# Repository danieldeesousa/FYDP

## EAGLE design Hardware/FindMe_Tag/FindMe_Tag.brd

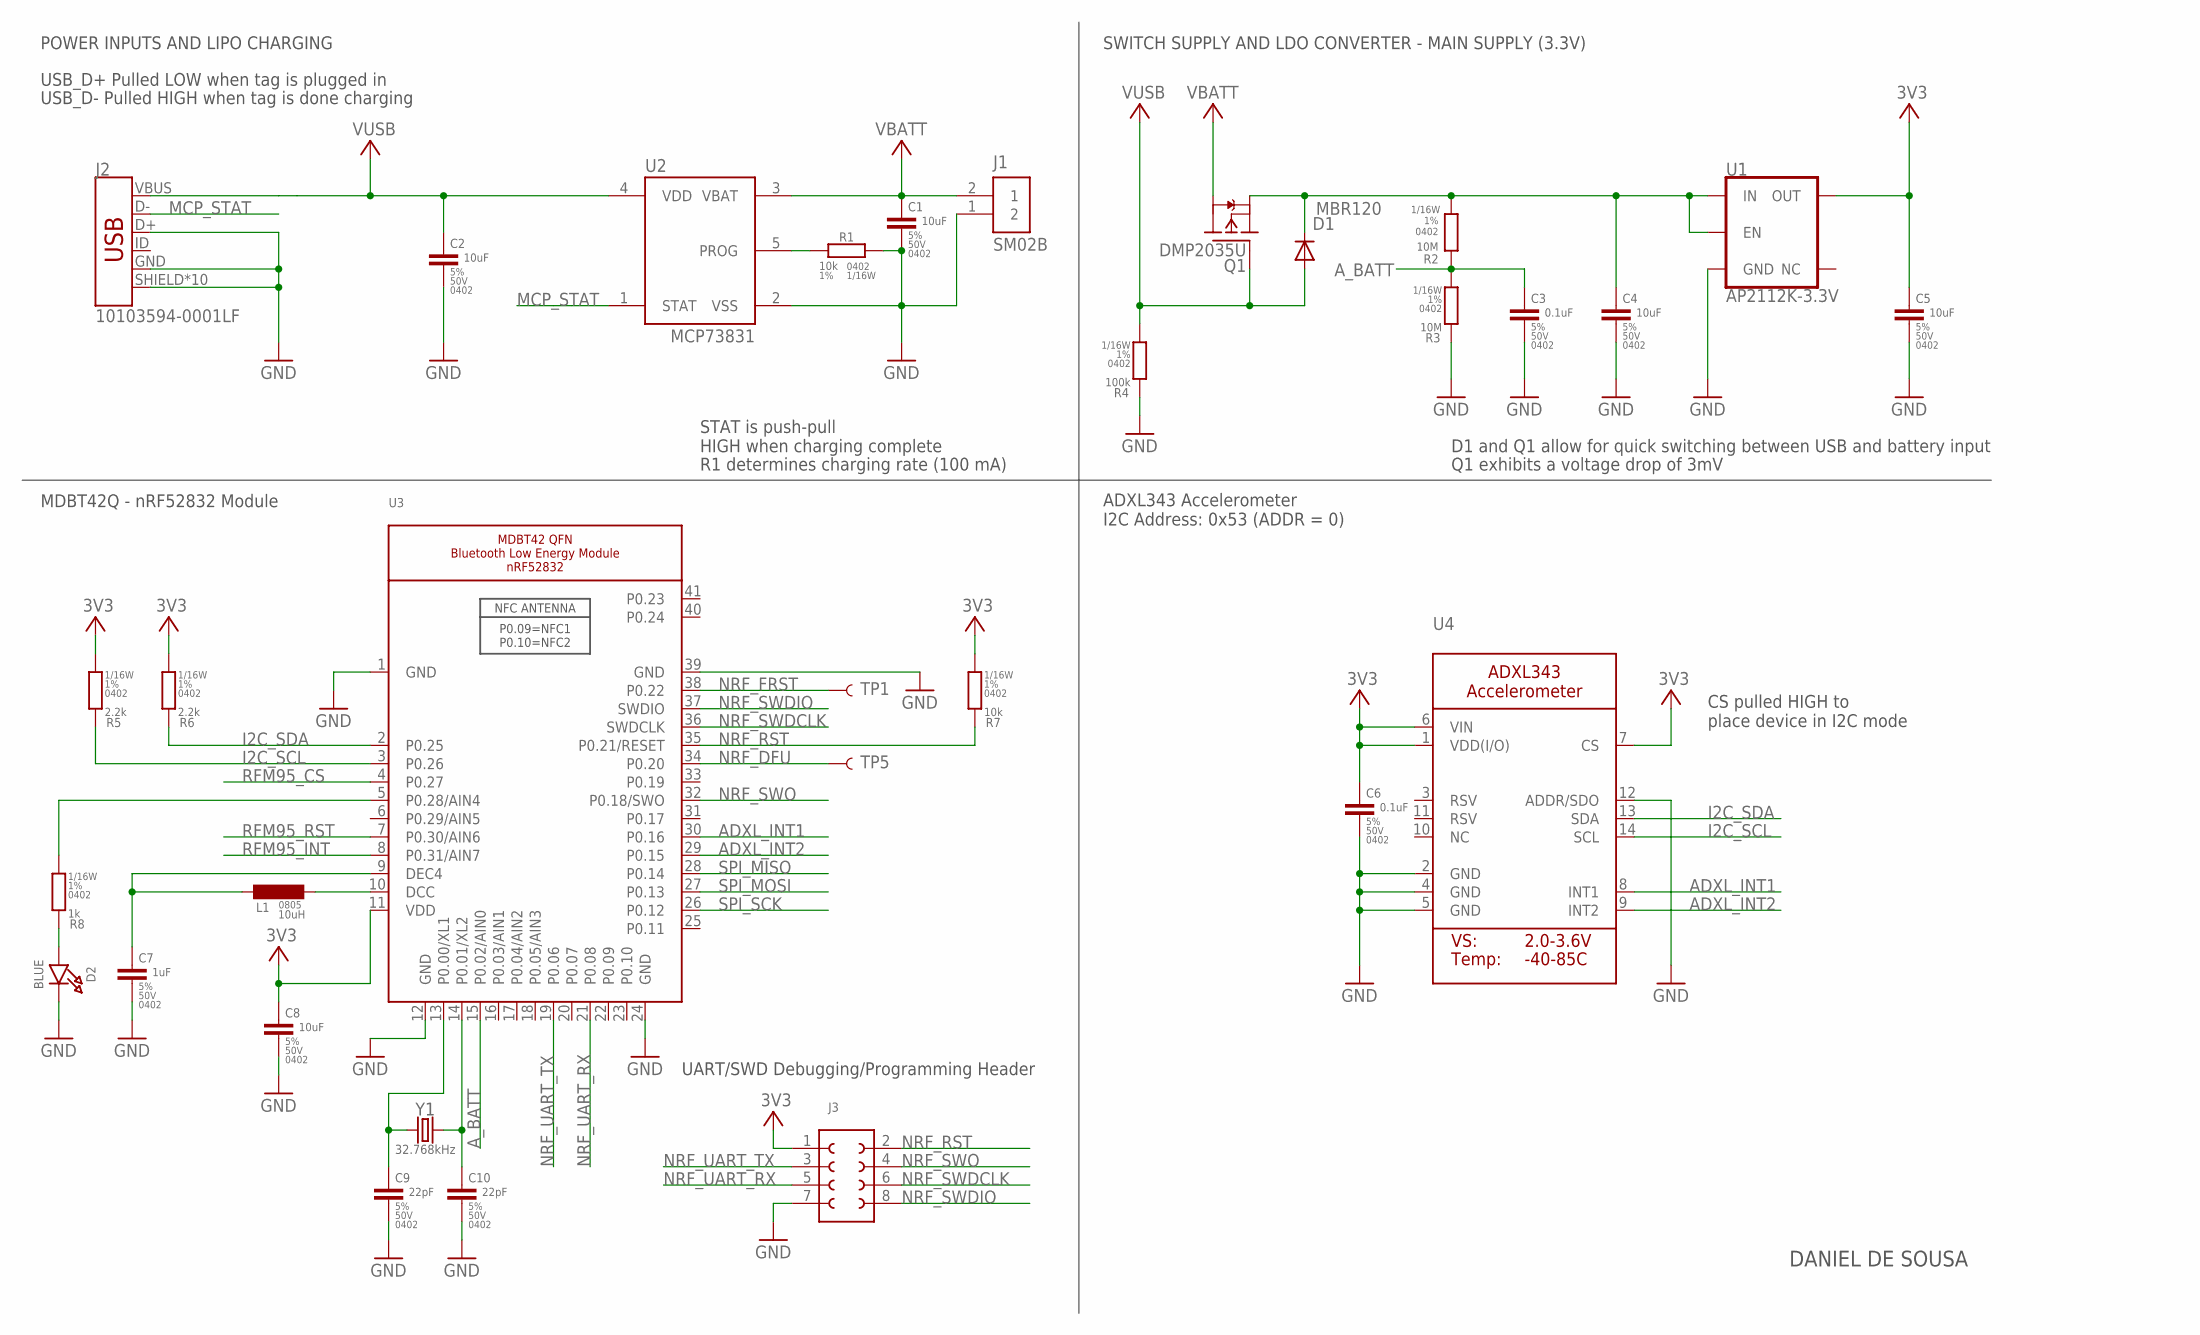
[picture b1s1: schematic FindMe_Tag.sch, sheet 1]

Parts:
C1, C2, C4, C5, C8: 10uF; C0402_MURATA_GRM15-GJM15
C3, C6: 0.1uF; C0402_MURATA_GRM15-GJM15
C7: 1uF; C0402_MURATA_GRM15-GJM15
C9, C10: 22pF; C0402_MURATA_GRM15-GJM15
D1: MBR120; SOD-123FL
D2: BLUE; CHIPLED_0805_NOOUTLINE
J1: SM02B; JST_SH_2X1
J2: 10103594-0001LF; USB-MICROB-PTH-MILL
J3: 610X08243021
L1: 10uH; L0805_MURATA_LQM21
Q1: DMP2035U; SOT23
R1, R7: 10k; R0402_VISHAY_CRCW0402
R2, R3: 10M; R0402_VISHAY_CRCW0402
R4: 100k; R0402_VISHAY_CRCW0402
R5, R6: 2.2k; R0402_VISHAY_CRCW0402
R8: 1k; R0402_VISHAY_CRCW0402
TP1, TP5: TEST-POINT3; PAD.03X.03
U1: AP2112K-3.3V; SOT23-5
U2: MCP73831; SOT-23
U3: NRF52832_MODULE_MDBT42; BLE_MODULE_RAYTAC_MDBT42
U4: ACCEL_ADXL343; LGA14
Y1: 32.768kHz; CRYSTAL-SMD-3.2X1.5MM

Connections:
+3V3: C5.1, C6.1, C8.1, J3.1, R5.2, R6.2, R7.2, U1.5 (OUT), U3.11 (VDD), U4.1 (VDD(I/O)), U4.6 (VIN), U4.7 (CS); also elsewhere on the board
ADXL_INT1: U3.30 (P0.16), U4.8 (INT1)
ADXL_INT2: U3.29 (P0.15), U4.9 (INT2)
A_BATT: C3.1, R2.1, R3.2, U3.15 (P0.02/AIN0)
GND: C1.2, C2.2, C3.2, C4.2, C5.2, C6.2, C7.2, C8.2, C9.2, C10.2, D2.C, J1.1 (2), J2.D+, J2.GND, J2.SHIELD, J2.SHIELD2 (SHIELD), J2.SHIELD3 (SHIELD), J2.SHIELD4 (SHIELD), J2.SHIELD5 (SHIELD), J2.SHIELD6 (SHIELD), J2.SHIELD7 (SHIELD), J2.SHIELD8 (SHIELD), J2.SHIELD9 (SHIELD), J2.SHIELD10 (SHIELD), J3.7 (4), R1.1, R3.1, R4.1, U1.2 (GND), U2.2 (VSS), U3.1 (GND), U3.12 (GND), U3.24 (GND), U3.39 (GND), U4.2 (GND), U4.4 (GND), U4.5 (GND), U4.12 (ADDR/SDO); also elsewhere on the board
I2C_SCL: R5.1, U3.3 (P0.26), U4.14 (SCL); also elsewhere on the board
I2C_SDA: R6.1, U3.2 (P0.25), U4.13 (SDA); also elsewhere on the board
MCP_STAT: J2.D-, U2.1 (STAT)
unnamed: R1.2, U2.5 (PROG)
unnamed: C4.1, D1.C, Q1.E (S), R2.2, U1.1 (IN), U1.3 (EN)
unnamed: C9.1, U3.13 (P0.00/XL1), Y1.P$1 (1)
unnamed: C10.1, U3.14 (P0.01/XL2), Y1.P$2 (2)
unnamed: L1.P$2 (2), U3.10 (DCC)
unnamed: C7.1, L1.P$1 (1), U3.9 (DEC4)
unnamed: R8.2, U3.5 (P0.28/AIN4)
unnamed: D2.A, R8.1
NRF_DFU: TP5.P$1, U3.34 (P0.20)
NRF_FRST: TP1.P$1, U3.38 (P0.22)
NRF_RST: J3.2 (8), R7.1, U3.35 (P0.21/RESET)
NRF_SWDCLK: J3.6, U3.36 (SWDCLK)
NRF_SWDIO: J3.8 (5), U3.37 (SWDIO)
NRF_SWO: J3.4 (7), U3.32 (P0.18/SWO)
NRF_UART_RX: J3.5 (3), U3.21 (P0.08)
NRF_UART_TX: J3.3 (2), U3.19 (P0.06)
RFM95_CS: U3.4 (P0.27); also elsewhere on the board
RFM95_INT: U3.8 (P0.31/AIN7); also elsewhere on the board
RFM95_RST: U3.7 (P0.30/AIN6); also elsewhere on the board
SPI_MISO: U3.28 (P0.14); also elsewhere on the board
SPI_MOSI: U3.27 (P0.13); also elsewhere on the board
SPI_SCK: U3.26 (P0.12); also elsewhere on the board
VBATT: C1.1, J1.2 (1), Q1.C (D), U2.3 (VBAT)
VUSB: C2.1, D1.A, J2.VBUS, Q1.B (G), R4.2, U2.4 (VDD)

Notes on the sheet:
ADXL343 Accelerometer I2C Address: 0x53 (ADDR = 0)
POWER INPUTS AND LIPO CHARGING
SWITCH SUPPLY AND LDO CONVERTER - MAIN SUPPLY (3.3V)
STAT is push-pull HIGH when charging complete
R1 determines charging rate (100 mA)
D1 and Q1 allow for quick switching between USB and battery input
DANIEL DE SOUSA
Q1 exhibits a voltage drop of 3mV
MDBT42Q - nRF52832 Module
USB_D- Pulled HIGH when tag is done charging
USB_D+ Pulled LOW when tag is plugged in
CS pulled HIGH to place device in I2C mode
UART/SWD Debugging/Programming Header

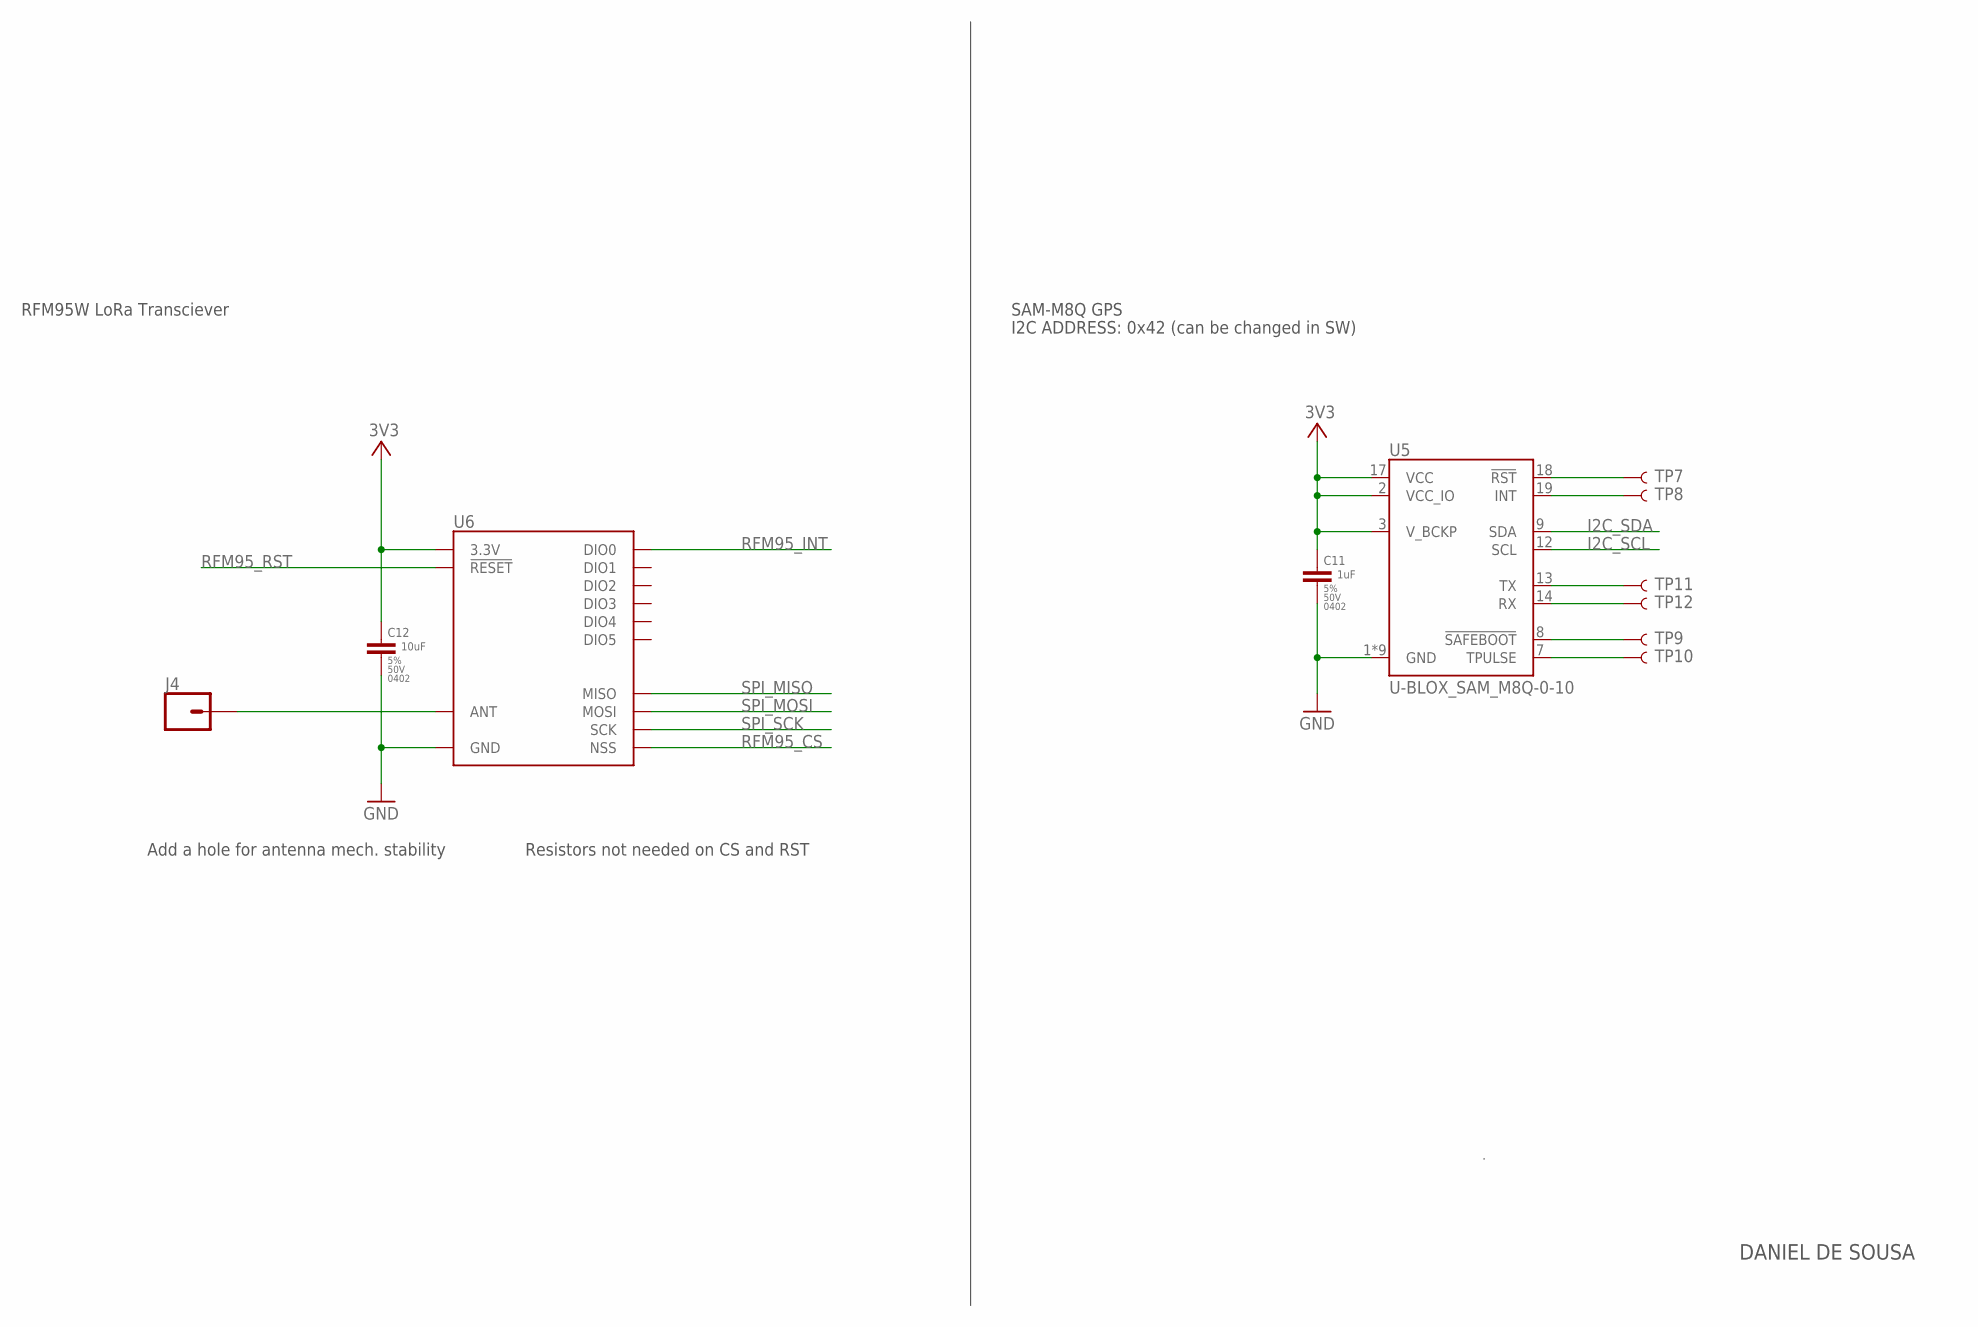
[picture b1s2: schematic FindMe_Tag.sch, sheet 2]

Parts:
C11: 1uF; C0402_MURATA_GRM15-GJM15
C12: 10uF; C0402_MURATA_GRM15-GJM15
J4: CONN_01PTH_NO_SILK_YES_STOP; 1X01_NO_SILK
TP7, TP8, TP9, TP10, TP11, TP12: TEST-POINT3; PAD.03X.03
U5: U-BLOX_SAM_M8Q-0-10; SAM-M8Q
U6: RFM95W; RFM95/96/97/98W

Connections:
+3V3: C11.1, C12.1, U5.2 (VCC_IO), U5.3 (V_BCKP), U5.17 (VCC), U6.3.3V; also elsewhere on the board
GND: C11.2, C12.2, U5.1 (GND), U5.4 (GND), U5.5 (GND), U5.6 (GND), U5.10 (GND), U5.11 (GND), U5.15 (GND), U5.16 (GND), U5.20 (GND), U6.GND@1 (GND), U6.GND@2 (GND), U6.GND@3 (GND); also elsewhere on the board
I2C_SCL: U5.12 (SCL); also elsewhere on the board
I2C_SDA: U5.9 (SDA); also elsewhere on the board
unnamed: J4.1, U6.ANT
unnamed: TP7.P$1, U5.18 (!RST)
unnamed: TP8.P$1, U5.19 (INT)
unnamed: TP9.P$1, U5.8 (!SAFEBOOT)
unnamed: TP10.P$1, U5.7 (TPULSE)
unnamed: TP11.P$1, U5.13 (TX)
unnamed: TP12.P$1, U5.14 (RX)
RFM95_CS: U6.NSS; also elsewhere on the board
RFM95_INT: U6.DIO0; also elsewhere on the board
RFM95_RST: U6.!RESET; also elsewhere on the board
SPI_MISO: U6.MISO; also elsewhere on the board
SPI_MOSI: U6.MOSI; also elsewhere on the board
SPI_SCK: U6.SCK; also elsewhere on the board

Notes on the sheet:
SAM-M8Q GPS
DANIEL DE SOUSA
I2C ADDRESS: 0x42 (can be changed in SW)
RFM95W LoRa Transciever
Resistors not needed on CS and RST
Add a hole for antenna mech. stability

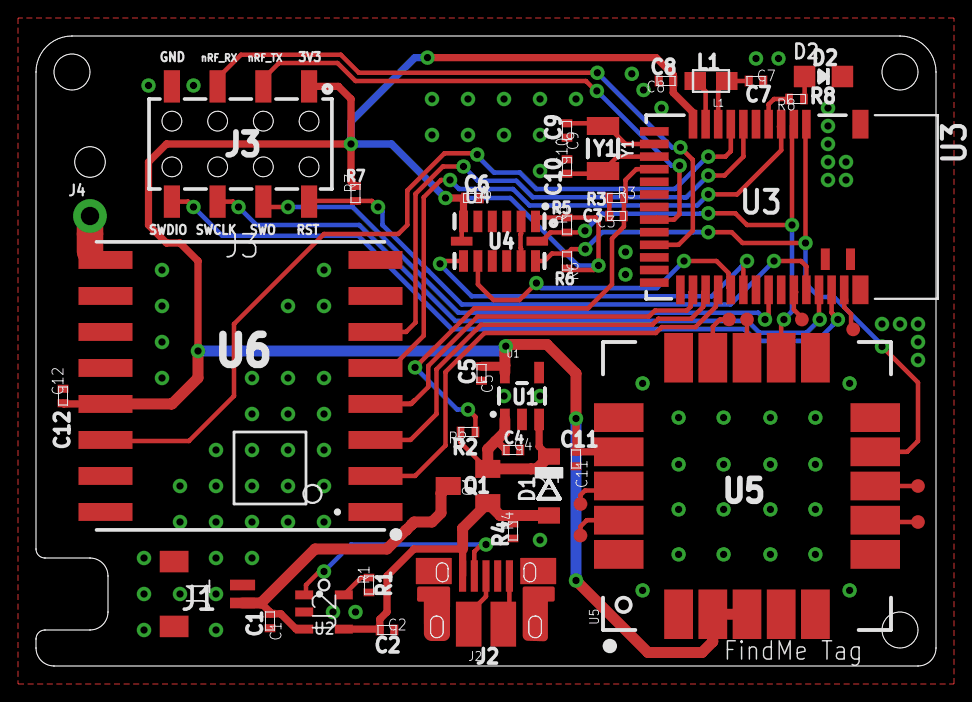
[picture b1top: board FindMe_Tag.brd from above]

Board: 2 copper layers, 50.0 x 35.0 mm, 43 parts (0 on the bottom side), 39 nets.

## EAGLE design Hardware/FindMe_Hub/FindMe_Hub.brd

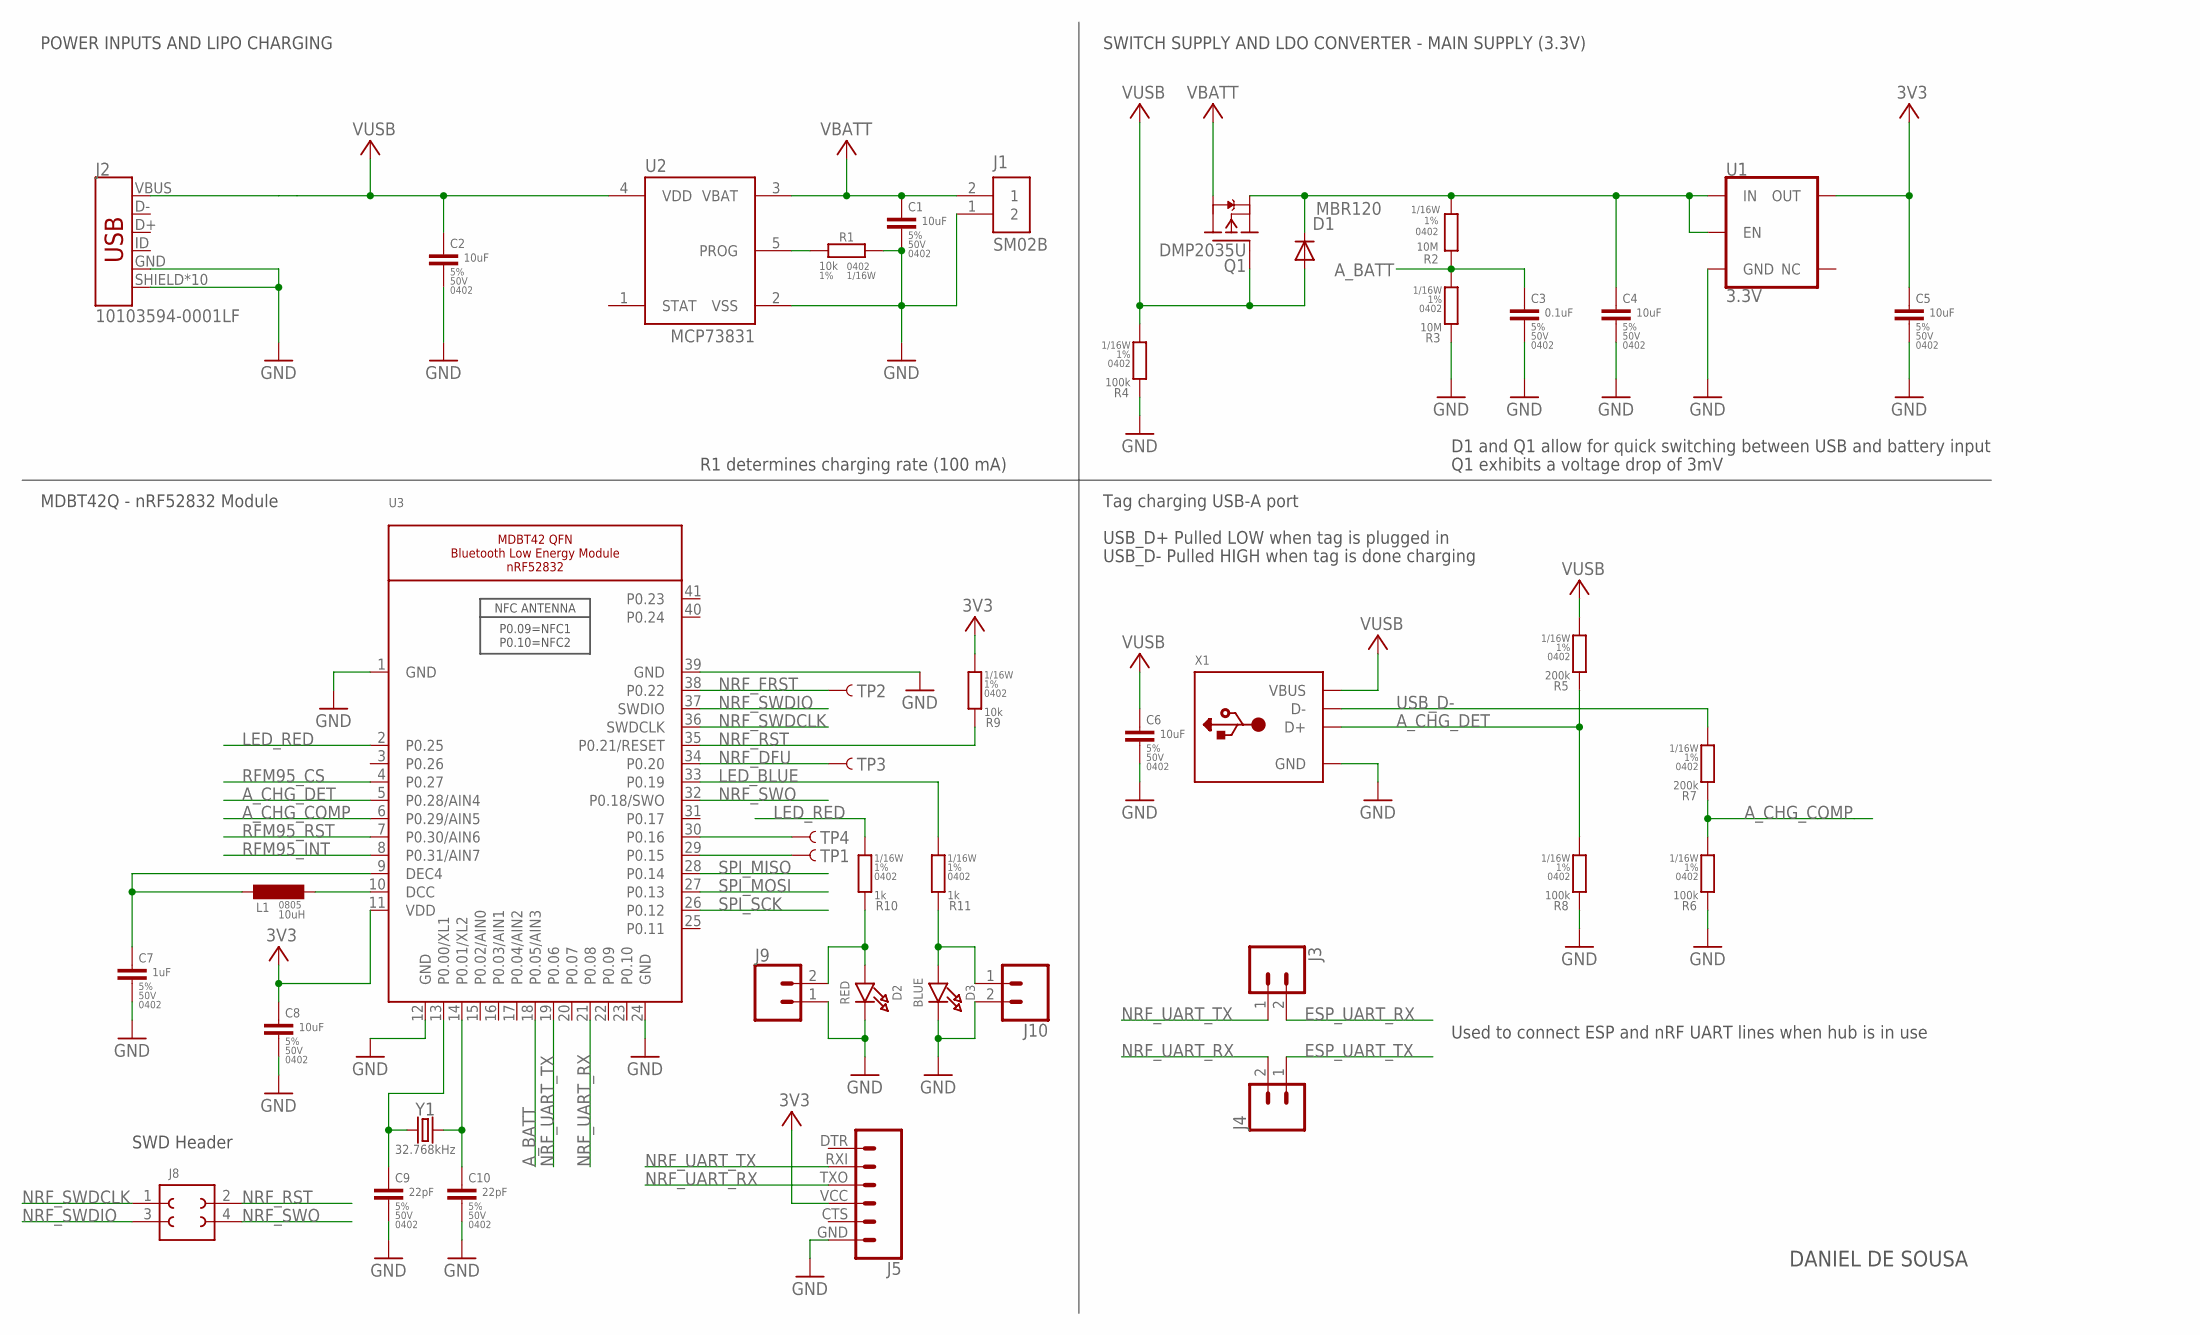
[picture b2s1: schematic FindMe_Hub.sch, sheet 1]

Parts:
C1, C2, C4, C5, C6, C8: 10uF; C0402_MURATA_GRM15-GJM15
C3: 0.1uF; C0402_MURATA_GRM15-GJM15
C7: 1uF; C0402_MURATA_GRM15-GJM15
C9, C10: 22pF; C0402_MURATA_GRM15-GJM15
D1: MBR120; SOD-123FL
D2: RED; CHIPLED_0805_NOOUTLINE
D3: BLUE; CHIPLED_0805_NOOUTLINE
J1: SM02B; JST_SH_2X1
J2: 10103594-0001LF; USB-MICROB-PTH-MILL
J3, J4, J9, J10: CONN_02; 1X02
J5: 6_PIN_SERIAL_CABLEPTH; FTDI_BASIC
J8: 610X0421121
L1: 10uH; L0805_MURATA_LQM21
Q1: DMP2035U; SOT23
R1, R9: 10k; R0402_VISHAY_CRCW0402
R2, R3: 10M; R0402_VISHAY_CRCW0402
R4, R6, R8: 100k; R0402_VISHAY_CRCW0402
R5, R7: 200k; R0402_VISHAY_CRCW0402
R10, R11: 1k; R0402_VISHAY_CRCW0402
TP1, TP2, TP3, TP4: TEST-POINT3X5; PAD.03X.05
U1: 3.3V; SOT23-5
U2: MCP73831; SOT-23
U3: NRF52832_MODULE_MDBT42; BLE_MODULE_RAYTAC_MDBT42
X1: USB_TYPEAPTHFML; USB_HOST-PTH
Y1: 32.768kHz; CRYSTAL-SMD-3.2X1.5MM

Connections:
+3V3: C5.1, C8.1, J5.VCC (4), R9.2, U1.5 (OUT), U3.11 (VDD); also elsewhere on the board
A_BATT: C3.1, R2.1, R3.2, U3.18 (P0.05/AIN3)
A_CHG_COMP: R6.2, R7.1, U3.6 (P0.29/AIN5)
A_CHG_DET: R5.1, R8.2, U3.5 (P0.28/AIN4), X1.D+
ESP_UART_RX: J3.2; also elsewhere on the board
ESP_UART_TX: J4.1; also elsewhere on the board
GND: C1.2, C2.2, C3.2, C4.2, C5.2, C6.2, C7.2, C8.2, C9.2, C10.2, D2.C, D3.C, J1.1 (2), J2.GND, J2.SHIELD, J2.SHIELD2 (SHIELD), J2.SHIELD3 (SHIELD), J2.SHIELD4 (SHIELD), J2.SHIELD5 (SHIELD), J2.SHIELD6 (SHIELD), J2.SHIELD7 (SHIELD), J2.SHIELD8 (SHIELD), J2.SHIELD9 (SHIELD), J2.SHIELD10 (SHIELD), J5.GND (6), J9.1, J10.2, R1.1, R3.1, R4.1, R6.1, R8.1, U1.2 (GND), U2.2 (VSS), U3.1 (GND), U3.12 (GND), U3.24 (GND), U3.39 (GND), X1.GND; also elsewhere on the board
LED_BLUE: R11.2, U3.33 (P0.19)
LED_RED: R10.2, U3.2 (P0.25)
unnamed: C9.1, U3.13 (P0.00/XL1), Y1.P$1 (1)
unnamed: R1.2, U2.5 (PROG)
unnamed: C4.1, D1.C, Q1.E (S), R2.2, U1.1 (IN), U1.3 (EN)
unnamed: C10.1, U3.14 (P0.01/XL2), Y1.P$2 (2)
unnamed: TP4.P$1, U3.30 (P0.16)
unnamed: TP1.P$1, U3.29 (P0.15)
unnamed: D2.A, J9.2, R10.1
unnamed: L1.P$2 (2), U3.10 (DCC)
unnamed: C7.1, L1.P$1 (1), U3.9 (DEC4)
unnamed: D3.A, J10.1, R11.1
NRF_DFU: TP3.P$1, U3.34 (P0.20)
NRF_FRST: TP2.P$1, U3.38 (P0.22)
NRF_RST: J8.2 (4), R9.1, U3.35 (P0.21/RESET)
NRF_SWDCLK: J8.1, U3.36 (SWDCLK)
NRF_SWDIO: J8.3 (2), U3.37 (SWDIO)
NRF_SWO: J8.4 (3), U3.32 (P0.18/SWO)
NRF_UART_RX: J4.2, J5.TXO (3), U3.21 (P0.08)
NRF_UART_TX: J3.1, J5.RXI (2), U3.19 (P0.06)
RFM95_CS: U3.4 (P0.27); also elsewhere on the board
RFM95_INT: U3.8 (P0.31/AIN7); also elsewhere on the board
RFM95_RST: U3.7 (P0.30/AIN6); also elsewhere on the board
SPI_MISO: U3.28 (P0.14); also elsewhere on the board
SPI_MOSI: U3.27 (P0.13); also elsewhere on the board
SPI_SCK: U3.26 (P0.12); also elsewhere on the board
USB_D-: R7.2, X1.D-
VBATT: C1.1, J1.2 (1), Q1.C (D), U2.3 (VBAT)
VUSB: C2.1, C6.1, D1.A, J2.VBUS, Q1.B (G), R4.2, R5.2, U2.4 (VDD), X1.VBUS; also elsewhere on the board

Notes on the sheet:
POWER INPUTS AND LIPO CHARGING
SWITCH SUPPLY AND LDO CONVERTER - MAIN SUPPLY (3.3V)
R1 determines charging rate (100 mA)
D1 and Q1 allow for quick switching between USB and battery input
DANIEL DE SOUSA
Q1 exhibits a voltage drop of 3mV
MDBT42Q - nRF52832 Module
USB_D- Pulled HIGH when tag is done charging
USB_D+ Pulled LOW when tag is plugged in
Used to connect ESP and nRF UART lines when hub is in use
Tag charging USB-A port
SWD Header

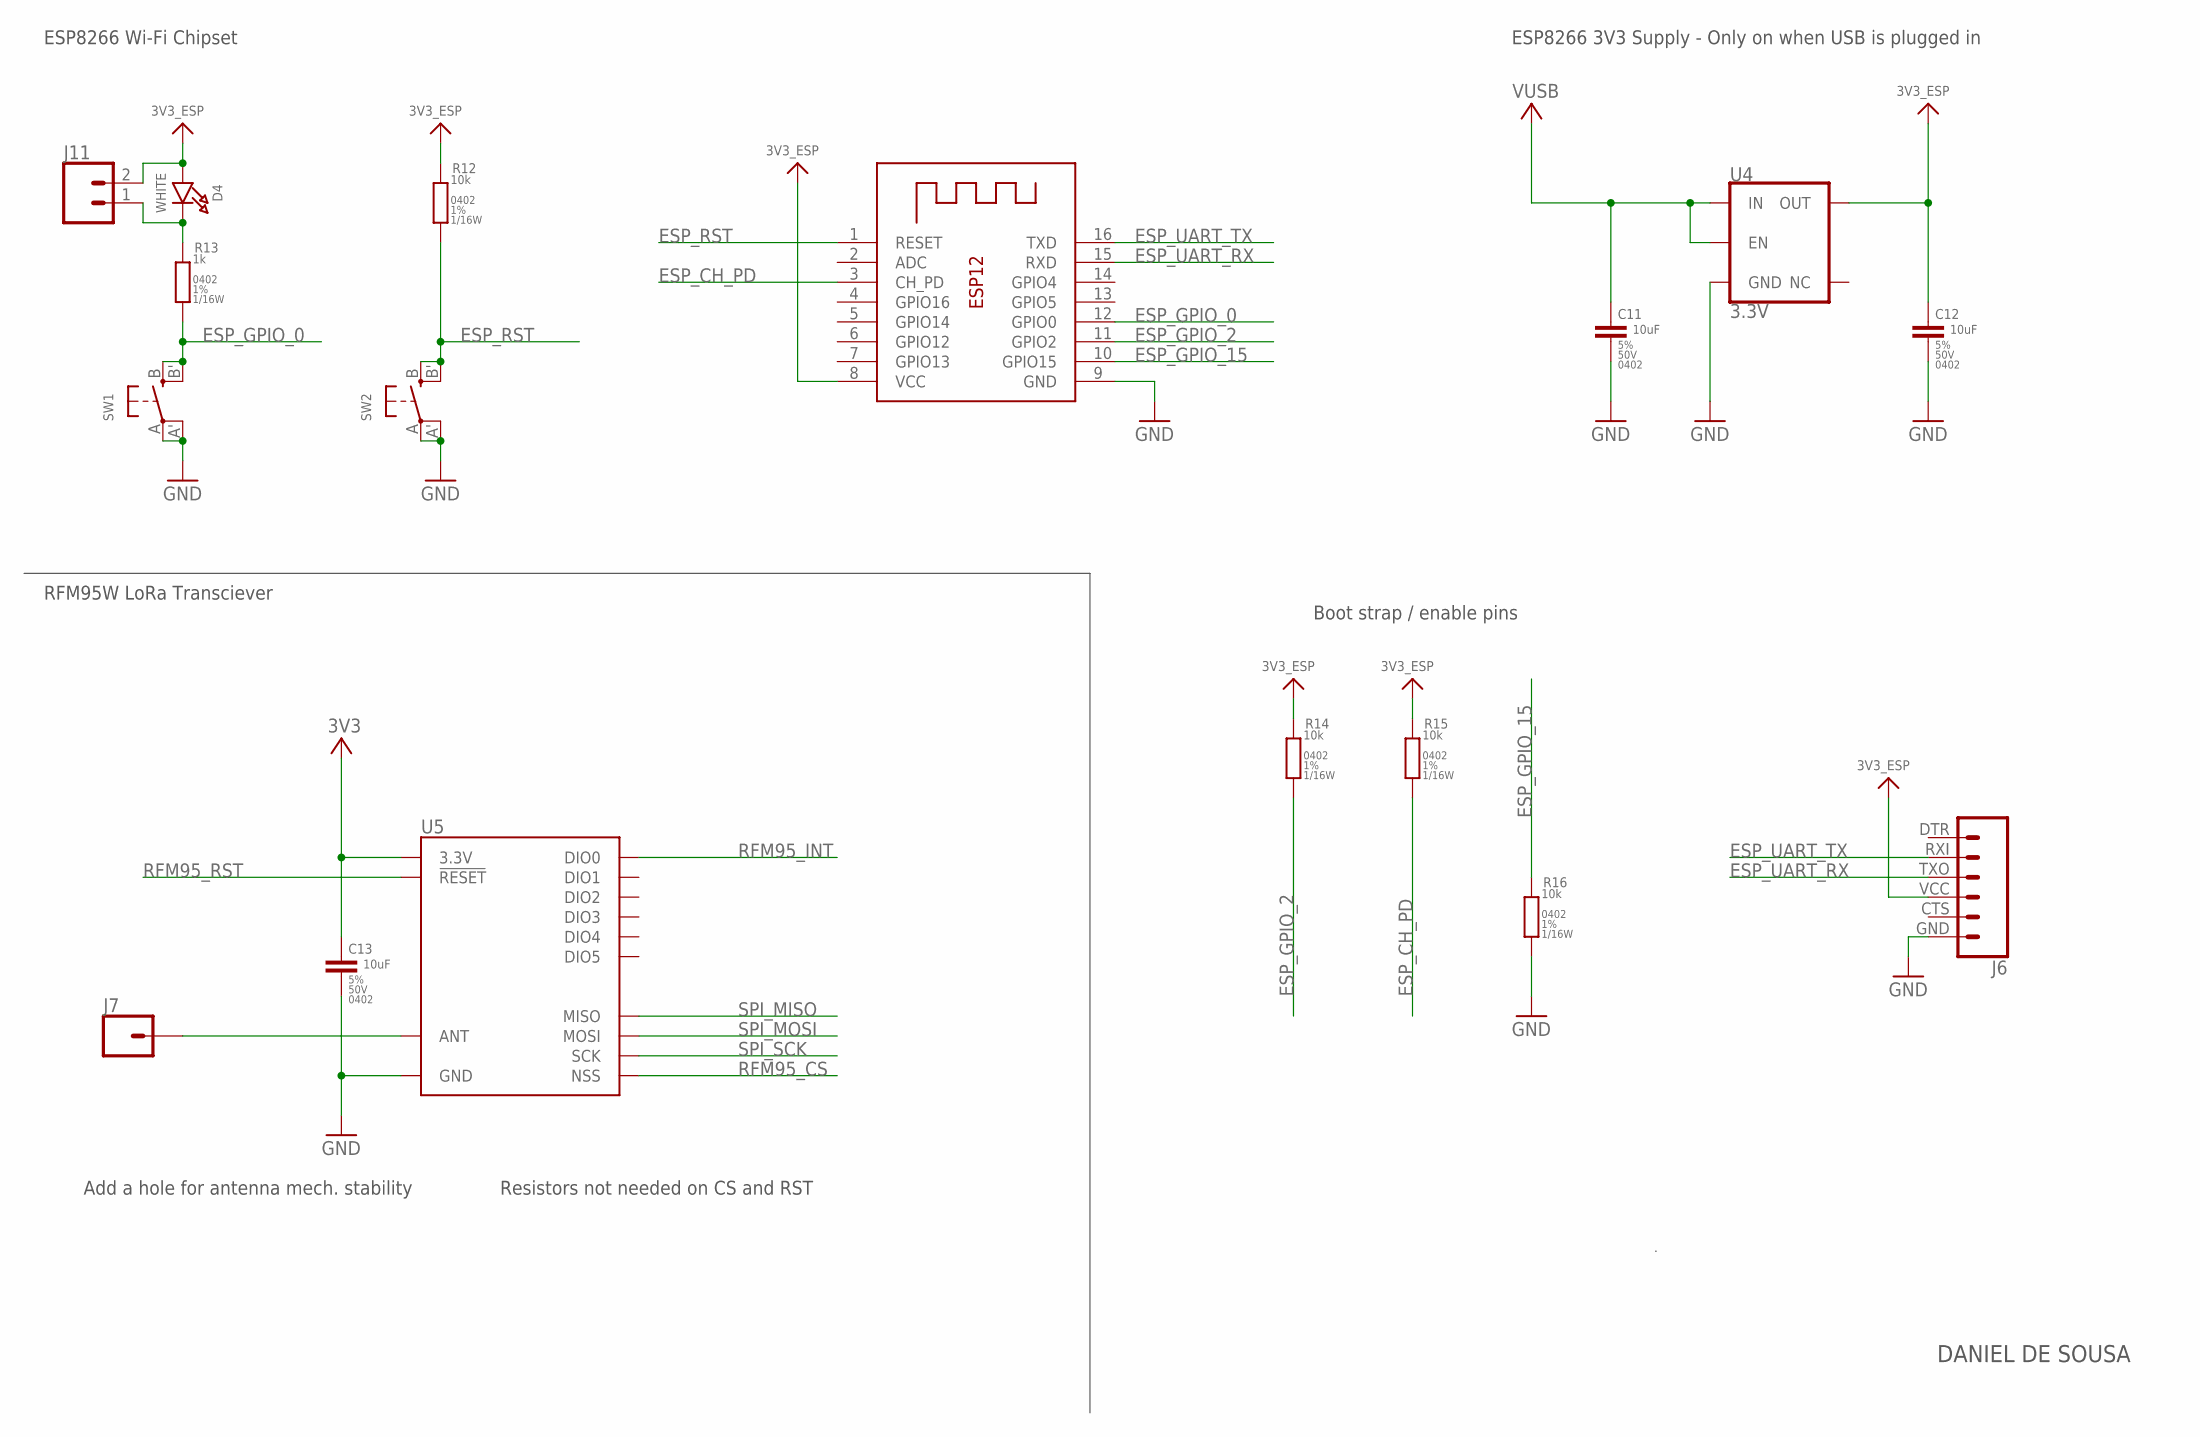
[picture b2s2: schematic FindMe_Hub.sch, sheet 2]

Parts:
C11, C12, C13: 10uF; C0402_MURATA_GRM15-GJM15
D4: WHITE; CHIPLED_0805_NOOUTLINE
J6: 6_PIN_SERIAL_CABLEPTH; FTDI_BASIC
J7: CONN_01PTH_NO_SILK_YES_STOP; 1X01_NO_SILK
J11: CONN_02; 1X02
R12, R14, R15, R16: 10k; R0402_VISHAY_CRCW0402
R13: 1k; R0402_VISHAY_CRCW0402
SW1, SW2: SWITCH_TACT_SMT4.6X2.8; BTN_KMR2_4.6X2.8
U4: 3.3V; SOT23-5
U5: RFM95W; RFM95/96/97/98W
X2: ESP-12

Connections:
+3V3: C13.1, U5.3.3V; also elsewhere on the board
ESP_CH_PD: R15.2, X2.3 (CH_PD)
ESP_GPIO_0: R13.2, SW1.B (S), SW1.B' (S1), X2.12 (GPIO0)
ESP_GPIO_2: R14.2, X2.11 (GPIO2)
ESP_GPIO_15: R16.1, X2.10 (GPIO15)
ESP_RST: R12.2, SW2.B (S), SW2.B' (S1), X2.1 (RESET)
ESP_UART_RX: J6.TXO (3), X2.15 (RXD); also elsewhere on the board
ESP_UART_TX: J6.RXI (2), X2.16 (TXD); also elsewhere on the board
GND: C11.2, C12.2, C13.2, J6.GND (6), R16.2, SW1.A, SW1.A' (P1), SW2.A, SW2.A' (P1), U4.2 (GND), U5.GND@1 (GND), U5.GND@2 (GND), U5.GND@3 (GND), X2.9 (GND); also elsewhere on the board
unnamed: J7.1, U5.ANT
unnamed: D4.C, J11.1, R13.1
RFM95_CS: U5.NSS; also elsewhere on the board
RFM95_INT: U5.DIO0; also elsewhere on the board
RFM95_RST: U5.!RESET; also elsewhere on the board
SPI_MISO: U5.MISO; also elsewhere on the board
SPI_MOSI: U5.MOSI; also elsewhere on the board
SPI_SCK: U5.SCK; also elsewhere on the board
VCCIO: C12.1, D4.A, J6.VCC (4), J11.2, R12.1, R14.1, R15.1, U4.5 (OUT), X2.8 (VCC)
VUSB: C11.1, U4.1 (IN), U4.3 (EN); also elsewhere on the board

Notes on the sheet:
RFM95W LoRa Transciever
ESP8266 Wi-Fi Chipset
DANIEL DE SOUSA
Resistors not needed on CS and RST
Add a hole for antenna mech. stability
Boot strap / enable pins
ESP8266 3V3 Supply - Only on when USB is plugged in

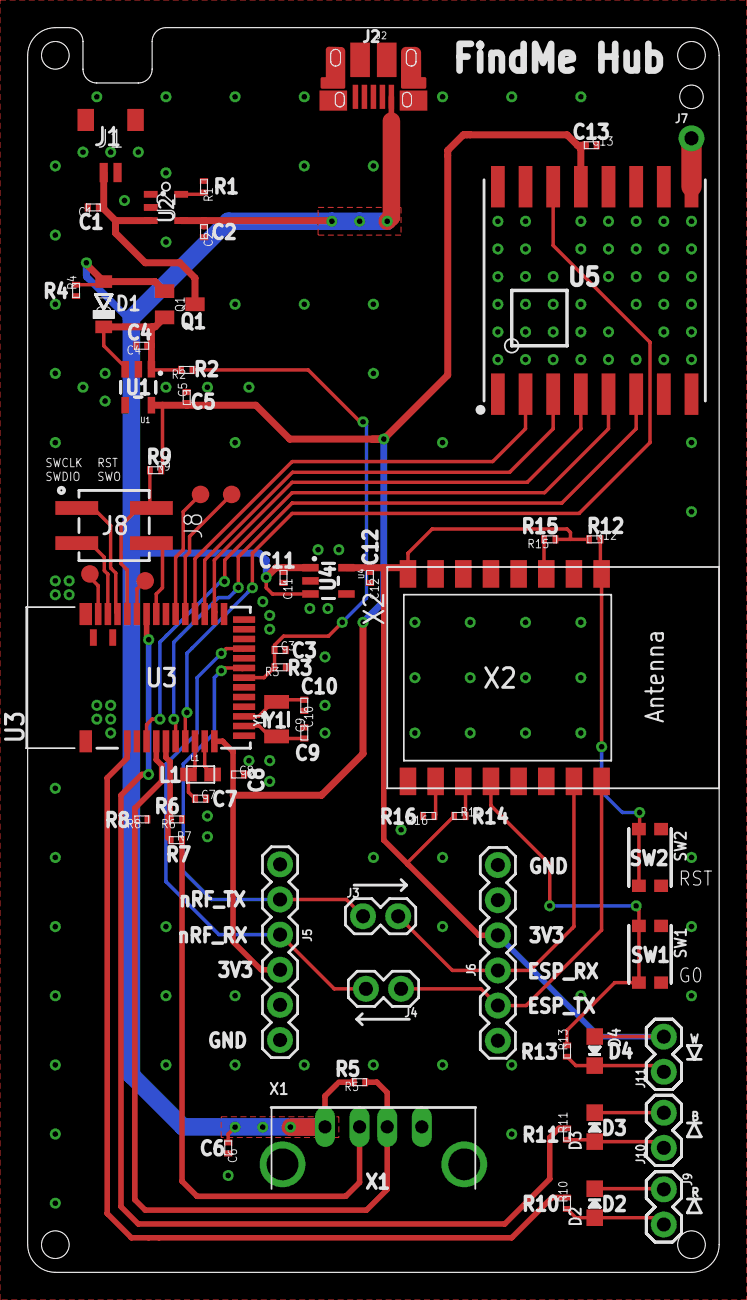
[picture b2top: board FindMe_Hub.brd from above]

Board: 2 copper layers, 50.0 x 90.0 mm, 60 parts (0 on the bottom side), 44 nets.

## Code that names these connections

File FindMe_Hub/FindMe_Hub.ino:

#include <string.h>
#include <bluefruit.h>
#include <SPI.h>
#include <RH_RF95.h>

// Disable/enable printlns
//#define Sprintln(a) (Serial.println(a)) // uncomment to ENABLE printlns
#define Sprintln(a) // uncomment to DISABLE printlns

// Pin definitions
#define RFM95_RST 30
#define RFM95_CS 27
#define RFM95_INT 31
#define BATTERY_VOLTAGE (A0) // change dependent on PCB
#define TAG_CHARGE_DET (A1) // change dependent on PCB
#define TAG_CHARGE_COMP (A2) // change dependent on PCB
#define WIFI_LED // driven on ESP8266
#define TAG_CHARGE_LED (15) // change dependent on PCB
#define BLE_LED (19) // driven by low-level BLE lib

// BLE services
BLEDfu bledfu; // OTA DFU service
BLEUart bleuart; // Uart over BLE service

// LoRa definitions
#define RF95_FREQ 915.0 // Can also be 434.0 - must match freq of chipset
RH_RF95 rf95(RFM95_CS, RFM95_INT); // Singleton instance of the radio driver

// Analog definitions
#define ADC_RES (1024.0) // default 10bit resolution - can be 8,10,12,14
#define REF_VOLTAGE (3.6) // Internal ADC reference voltage
#define VOLTAGE_USB (4.5) // Voltage detected when USB is in

// Application variables
#define RSSI_BUF_SIZE 5
int16_t rssiBuf[RSSI_BUF_SIZE]; // used to average RSSI value
int8_t rssiBuf_idx = 0;
int16_t averageRSSI;
bool isBLEConnected = 0; // 1 if connected, 0 if not

// BLE connection callbacks
void prph_connect_callback(uint16_t conn_handle)
{
  isBLEConnected = true;
}
void prph_disconnect_callback(uint16_t conn_handle, uint8_t reason)
{
  isBLEConnected = false;
}

void setup(void)
{
  Serial.begin(9600);
  Sprintln("FindMe - Hub booted");
  
  // Demo LED
  pinMode(TAG_CHARGE_LED, OUTPUT);
  pinMode(BLE_LED, OUTPUT);

  setupBLE();
  setupLoRa();
}

void loop(void)
{
  // Check if tag is plugged in
  float tagChargeVoltage = (analogRead(TAG_CHARGE_DET) / ADC_RES) * REF_VOLTAGE;

  // TAG LED charging behaviour: flashing (charging), solid (charge complete)
  if(tagChargeVoltage > 1)
  {
    digitalWrite(TAG_CHARGE_LED, HIGH);
  }
  
  // Check LoRa
  recieveLoRaPacket();
  delay(1000);

  // TAG LED charging behaviour: flashing (charging), solid (charge complete)
  // TODO: check here is charge complete (dont turn off LED when charge complete)
  if(tagChargeVoltage > 1)
  {
    digitalWrite(TAG_CHARGE_LED, LOW);
  }

  // Check ESP Serial port
  readSerial();
  delay(1000); 
}

static char input[20];
static int idx = 0;
void readSerial()
{
  while(Serial.available() > 0)
  {
    // append to array
    input[idx] = Serial.read();
    idx++;
    
    // check if end of message
    if(input[idx-1] == '\n')
    {
      input[idx-1] = '\0';
      if(strncmp(input, "FRCD-RQST", 9) == 0)
      {
        sendForcedRqst();
      }

      // clear buffer
      idx = 0;
      input[0] = '\0';
    }

    // check for buffer overflow
    if(idx >= 10)
    {
      // clear buffer
      idx = 0;
      input[0] = '\0';
    }
  }
}

void recieveLoRaPacket()
{
  digitalWrite(LED_BUILTIN, HIGH);
  
  // Wait for LoRa message
  if (rf95.available())
  {
    // Should be a message for us now
    uint8_t buf[RH_RF95_MAX_MESSAGE_LEN];
    uint8_t len = sizeof(buf);;
    if (rf95.recv(buf, &len))
    {
      // Terminate message
      buf[len] = '\0';
      
      // Print packet
      Sprintln("LoRa RX: ");
      Sprintln((char*)buf);

      // Determine whether to send over Wi-Fi
      // Check if USB is connected
      // *2 because of voltage divider
      float battVoltage = 2*(analogRead(BATTERY_VOLTAGE) / ADC_RES) * REF_VOLTAGE;
      //if(battVoltage > VOLTAGE_USB)
      if(1)
      {
        // Send LoRa packet to ESP to process
        Serial.write((char*)buf);
        Serial.write("\n");
      }

      // Determine whether to send over BLE
      if(isBLEConnected == true)
      {
        // Remove battery and alert info
        // Confirm with FYDP team
        buf[16] = '\0';
        
        // Get RSSI
        Sprintln(rf95.lastRssi());
        rssiBuf[rssiBuf_idx++] = rf95.lastRssi();
        rssiBuf_idx %= RSSI_BUF_SIZE;
    
        // Calcute average RSSI
        averageRSSI = 0; // reset
        for (int i = 0; i < RSSI_BUF_SIZE; i++){
           averageRSSI += rssiBuf[i]; // add up all RSSIs
        }
        averageRSSI /= RSSI_BUF_SIZE; // determine average by dividing by size of array
        
        // Add RSSI to data packet
        sprintf((char*)buf, "%s%d", buf, rf95.lastRssi());
        //Sprintln((char*)buf);
        
        // Send this data over BLE
        bleuart.print((char*)buf);
      }
    }
  }      

  digitalWrite(LED_BUILTIN, LOW);
}

void sendForcedRqst()
{
  digitalWrite(LED_BUILTIN, HIGH);

  // Enable transmitter
  delay(100);
  rf95.setModeTx();
  delay(100);

  // Send forced request LoRa message
  const uint8_t forcedReqBuf[] = "FRCD-RQST";
  uint8_t len = sizeof(forcedReqBuf);
  rf95.send(forcedReqBuf, len);
  delay(10);
  rf95.waitPacketSent(); // blocks until transmitter is no longer transmitting
  
  // Put transciever back in RX mode
  delay(100);
  rf95.setModeRx();
  delay(100);
  
  digitalWrite(LED_BUILTIN, LOW);
}



/////////////////////////////////////////////////////////////
//////////// HELPER FUNCTIONS ///////////////////////////////
/////////////////////////////////////////////////////////////

void setupBLE()
{
  // Setup BLE
  Bluefruit.begin();
  
  //TODO: Tune this value (maximize range, minimize power)
  Bluefruit.setTxPower(4);    // Check bluefruit.h for supported values
  Bluefruit.setName("FindMe - Hub");

  // Callbacks for Peripheral
  Bluefruit.Periph.setConnectCallback(prph_connect_callback);
  Bluefruit.Periph.setDisconnectCallback(prph_disconnect_callback);
  
  // Start services
  bledfu.begin(); //To be consistent, OTA DFU should be added first if it exists
  bleuart.begin(); // Configure and start the BLE Uart service
  
  // Set up and start advertising
  startAdv();
}

void setupLoRa()
{
  // Setup LoRa
  pinMode(RFM95_RST, OUTPUT);
  digitalWrite(RFM95_RST, HIGH);
  
  // Manual reset
  digitalWrite(RFM95_RST, LOW);
  delay(10);
  digitalWrite(RFM95_RST, HIGH);
  delay(10);
  
  // Initialize LoRa
  while (!rf95.init()) {
    Sprintln("LoRa radio init failed");
    Sprintln("Uncomment '#define SERIAL_DEBUG' in RH_RF95.cpp for detailed debug info");
    digitalWrite(LED_BUILTIN, HIGH);
    while (1);
  }
  Sprintln("LoRa radio init OK!");
  
  // Defaults after init are 434.0MHz, modulation GFSK_Rb250Fd250, +13dbM
  if (!rf95.setFrequency(RF95_FREQ)) {
    Sprintln("setFrequency failed");
    digitalWrite(LED_BUILTIN, HIGH);
    while (1);
  }

  // Defaults after init are 434.0MHz, 13dBm, Bw = 125 kHz, Cr = 4/5, Sf = 128chips/symbol, CRC on
  // The default transmitter power is 13dBm, using PA_BOOST.
  // If you are using RFM95/96/97/98 modules which uses the PA_BOOST transmitter pin, then
  // you can set transmitter powers from 5 to 23 dBm:
  // False uses PA_BOOST pins (RF95)
  rf95.setTxPower(23, false);

  // Start transciever in RX mode
  rf95.setModeRx();
}

void startAdv(void)
{
  // Advertising packet
  Bluefruit.Advertising.addFlags(BLE_GAP_ADV_FLAGS_LE_ONLY_GENERAL_DISC_MODE);
  Bluefruit.Advertising.addTxPower();
  
  // Include the BLE UART (AKA 'NUS') 128-bit UUID
  Bluefruit.Advertising.addService(bleuart);

  // Secondary Scan Response packet (optional)
  // Since there is no room for 'Name' in Advertising packet
  Bluefruit.ScanResponse.addName();

  /* Start Advertising
   * - Enable auto advertising if disconnected
   * - Interval:  fast mode = 20 ms, slow mode = 152.5 ms
   * - Timeout for fast mode is 30 seconds
   * - Start(timeout) with timeout = 0 will advertise forever (until connected)
   * 
   * For recommended advertising interval
   * https://developer.apple.com/library/content/qa/qa1931/_index.html   
   */
  Bluefruit.Advertising.restartOnDisconnect(true);
  Bluefruit.Advertising.setInterval(32, 244);    // in unit of 0.625 ms
  Bluefruit.Advertising.setFastTimeout(30);      // number of seconds in fast mode
  Bluefruit.Advertising.start(0);                // 0 = Don't stop advertising after n seconds  
}

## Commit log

2020-01-27 :circus_tent: Added .gitattributes & .gitignore files
2020-02-02 Full-featured hub and tag fw
2020-02-14 FW V1
2020-02-28 Hardware finalized
2020-03-01 Wi-Fi disconnect
2020-03-01 Wi-fi fixes
2020-03-02 Added BLE encoding, LPM
2020-03-11 Added libs, symposim update

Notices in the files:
parts and their libraries:
microbuilder: This work is placed in the public domain, and may be freely used for commercial and non-commercial work with the following conditions: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
SparkFun-Connectors: Licensing: Creative Commons ShareAlike 4.0 International - https://creativecommons.org/licenses/by-sa/4.0
